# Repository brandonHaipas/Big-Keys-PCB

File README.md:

# Big-Keys-PCB

In this repository I will be updating the files needed to print the PCB for the InCA:Big-Keys keyboard, which aim is to augmentate communication between human and non-human animals, specifically medium size non-human animals.
I'll be updating more details in [the project's page](https://bigkeys.incalab.cl/).
For the development of this project I followed the mechanical PCB guide made by ai03, [here's the guide](https://wiki.ai03.com/books/pcb-design/chapter/pcb-designer-guide) if you want to create your own keypad or keyboard.

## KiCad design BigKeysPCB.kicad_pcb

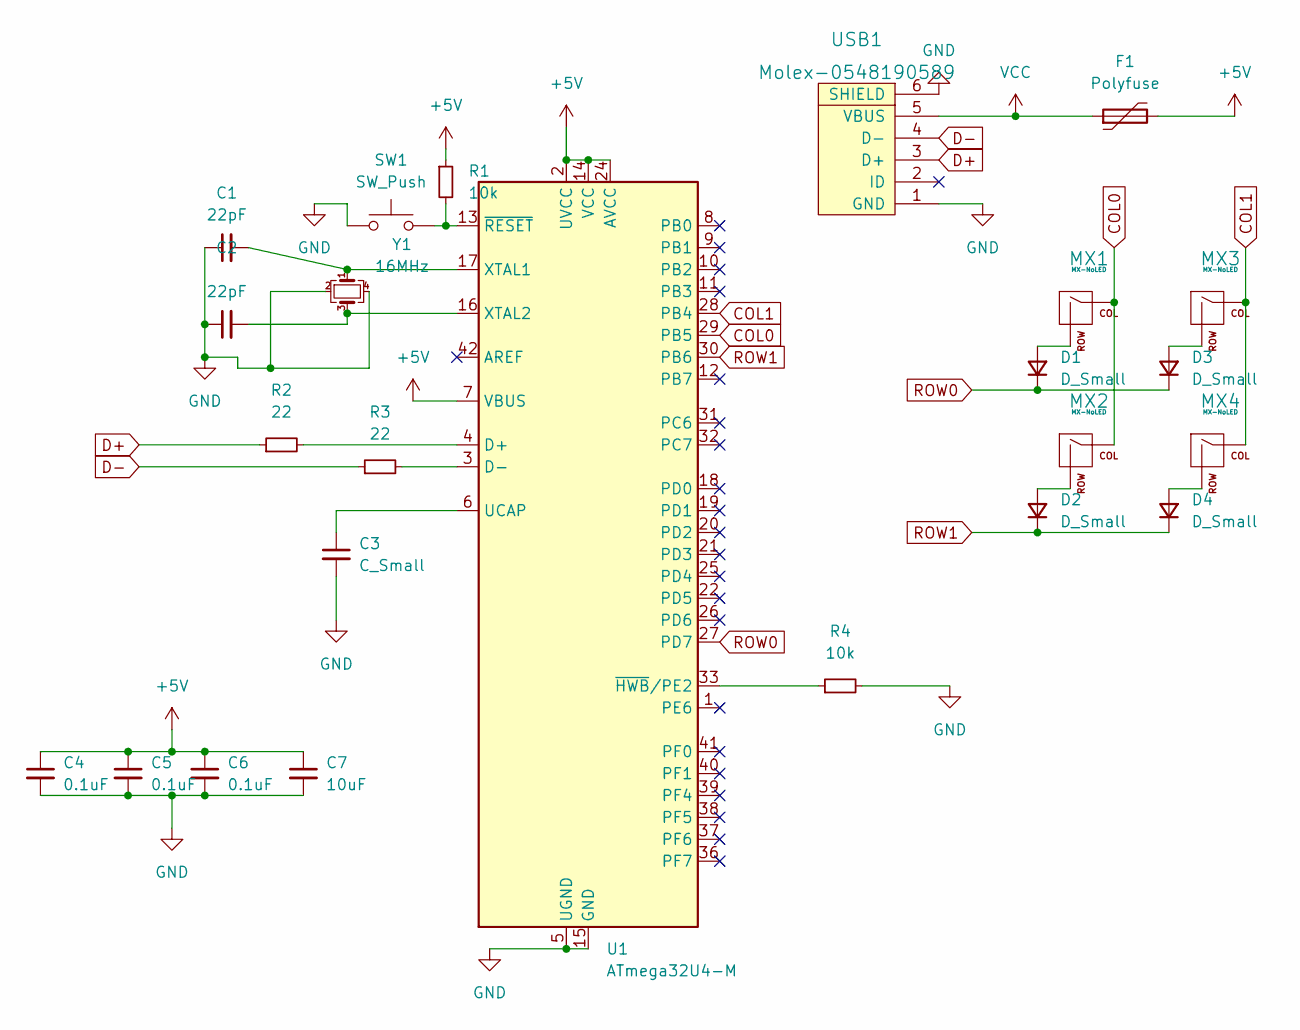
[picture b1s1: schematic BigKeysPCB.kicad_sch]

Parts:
C1, C2: 22pF; C_0805_2012Metric
C3: C_Small; C_0805_2012Metric
C4, C5, C6: 0.1uF; C_0805_2012Metric
C7: 10uF; C_0805_2012Metric
D1, D2, D3, D4: D_Small; D_SOD-123
F1: Polyfuse; Fuse_1206_3216Metric
MX1, MX2, MX3, MX4: MX-NoLED; MX-1U
R1, R4: 10k; R_0805_2012Metric
R2, R3: 22; R_0805_2012Metric
SW1: SW_Push; SKQG-1155865
U1: ATmega32U4-M; QFN-44-1EP_7x7mm_P0.5mm_EP5.2x5.2mm
USB1: Molex-0548190589
Y1: 16MHz; Crystal_SMD_3225-4Pin_3.2x2.5mm

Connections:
+5V: C4.1, C5.1, C6.1, C7.1, F1.2, R1.1, U1.2 (UVCC), U1.7 (VBUS), U1.14 (VCC), U1.24 (AVCC), U1.34 (VCC), U1.44 (AVCC)
COL0: MX1.1 (COL), MX2.1 (COL), U1.29 (PB5)
COL1: MX3.1 (COL), MX4.1 (COL), U1.28 (PB4)
D+: R2.1, USB1.3 (D+)
D-: R3.1, USB1.4 (D-)
GND: C1.1, C2.1, C3.2, C4.2, C5.2, C6.2, C7.2, R4.2, SW1.1, U1.5 (UGND), U1.15 (GND), U1.23 (GND), U1.35 (GND), U1.43 (GND), U1.45 (GND), USB1.1 (GND), USB1.6 (SHIELD), Y1.2, Y1.4
unnamed: C1.2, U1.17 (XTAL1), Y1.1
unnamed: C2.2, U1.16 (XTAL2), Y1.3
unnamed: C3.1, U1.6 (UCAP)
unnamed: D1.2 (A), MX1.2 (ROW)
unnamed: D2.2 (A), MX2.2 (ROW)
unnamed: D3.2 (A), MX3.2 (ROW)
unnamed: D4.2 (A), MX4.2 (ROW)
unnamed: R1.2, SW1.2, U1.13 (~RESET)
unnamed: R2.2, U1.4 (D+)
unnamed: R3.2, U1.3 (D-)
unnamed: R4.1, U1.33 (~HWB/PE2)
ROW0: D1.1 (K), D3.1 (K), U1.27 (PD7)
ROW1: D2.1 (K), D4.1 (K), U1.30 (PB6)
VCC: F1.1, USB1.5 (VBUS)

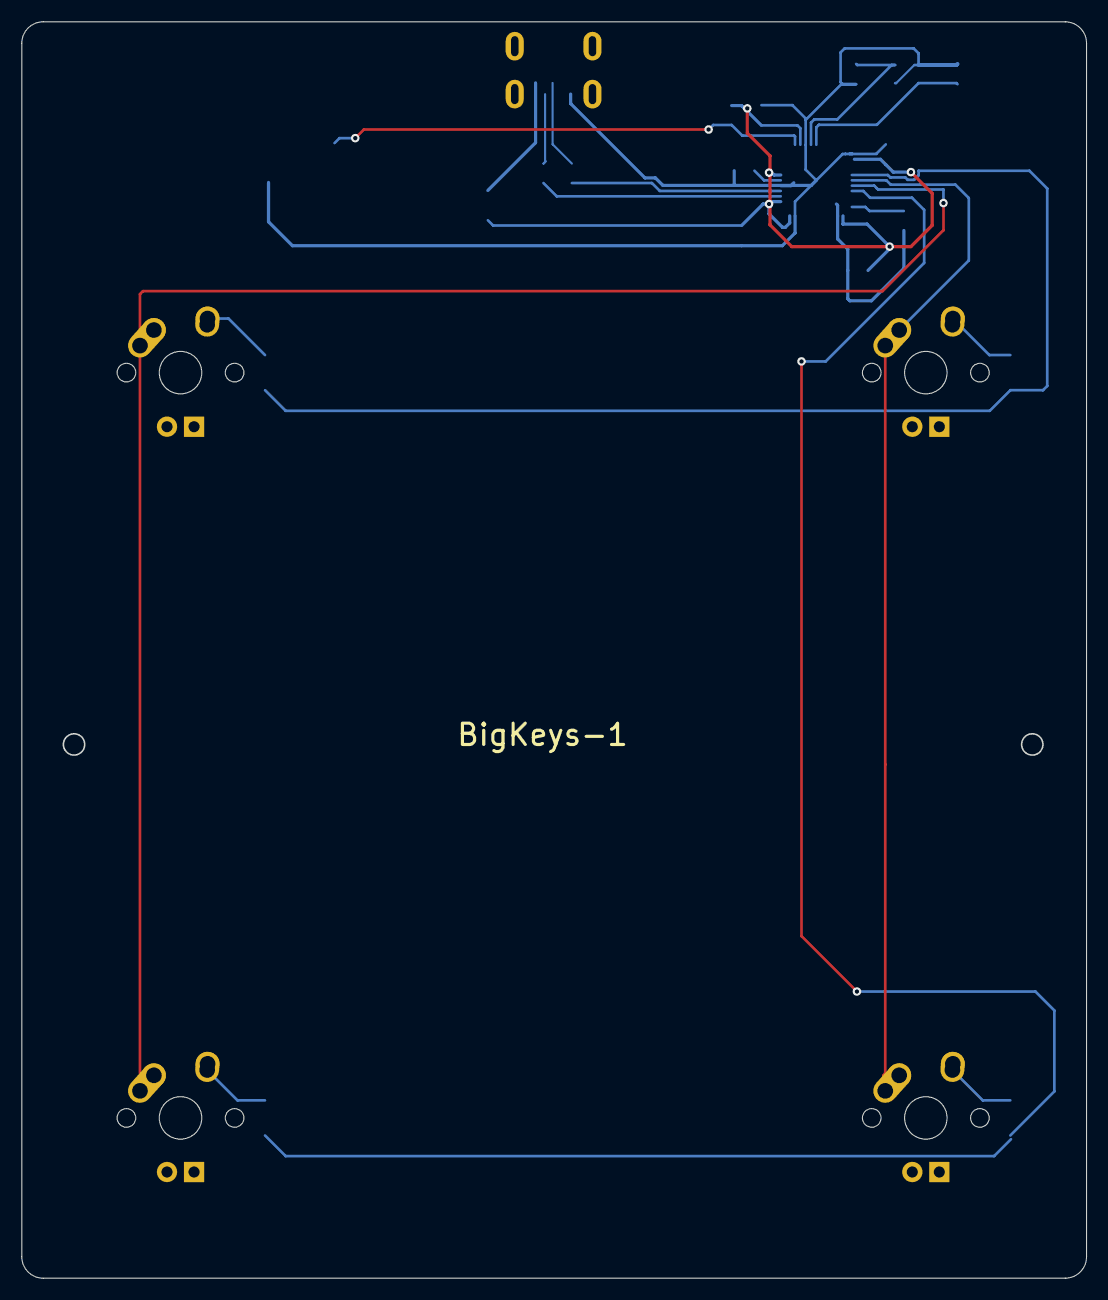
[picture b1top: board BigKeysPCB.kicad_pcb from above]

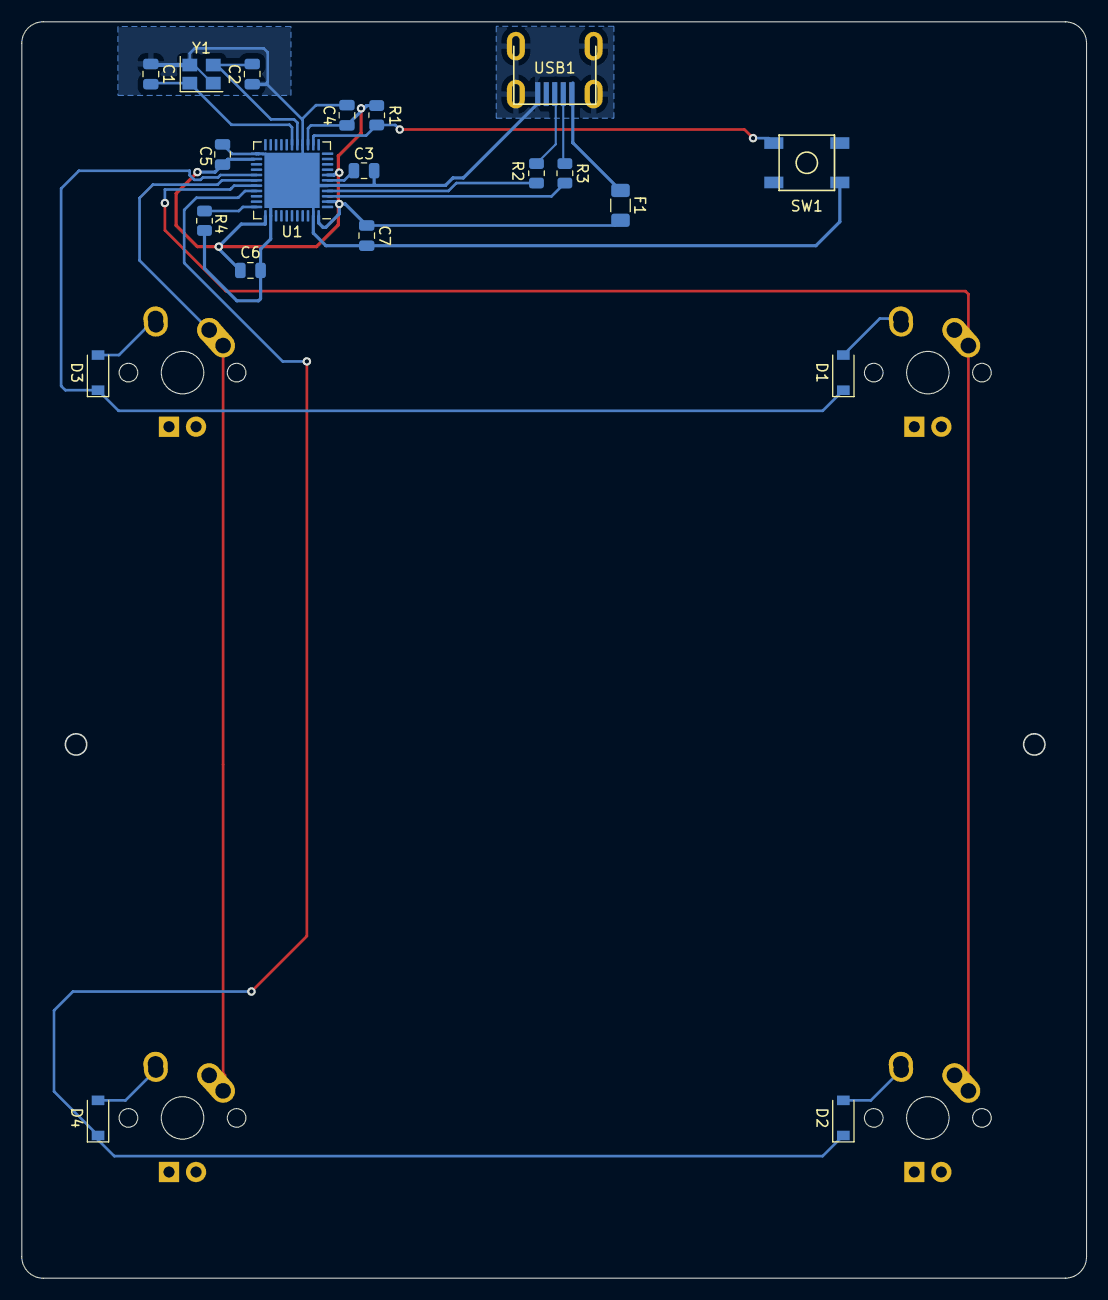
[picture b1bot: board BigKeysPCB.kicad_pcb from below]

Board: 2 copper layers, 100.0 x 118.0 mm, 24 parts (20 on the bottom side), 20 nets.

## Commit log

2022-10-18 License created
2022-10-18 Readme created
2022-10-18 Add submodules
2022-10-18 libraries added as local in both schematics and PCB files
2022-10-18 MCU schematics done
2022-10-18 schematics and footprint bindings ready for importing to PCB layout
2022-10-18 preliminary PCB design
2022-11-09 first prototype finished
2022-11-10 changed the soldering mask color from green to red
2022-11-10 readme changed, credits added for ai03
2022-11-10 changed plate moount holes dimensions to fit M2 screws
2022-11-10 changed wiring, some errors and warnings solved
2022-11-11 correct measures for 3D case and plate model
2022-11-14 shield connected to ground, missing connection added to pcb file
2022-11-16 mx-only library added to the PCB file
2023-01-16 most of ERC and ERC errors debugged
2023-01-16 final version of first prototype
